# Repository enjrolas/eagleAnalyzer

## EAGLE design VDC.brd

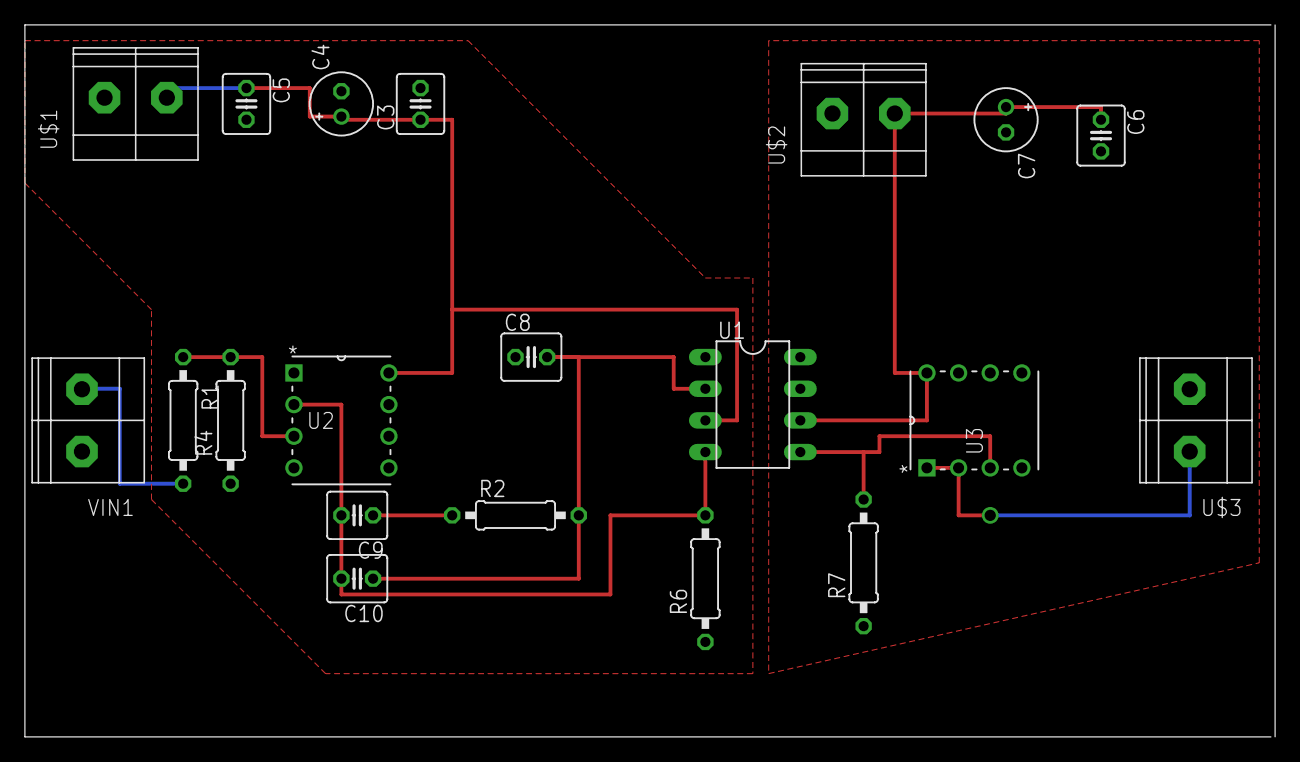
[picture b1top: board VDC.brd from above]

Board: 2 copper layers, 100.3 x 57.1 mm, 20 parts (0 on the bottom side), 11 nets.

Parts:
C3, C5, C6, C8, C9, C10: C025-040X050
C4, C7: E2-5
R1, R2, R4, R6, R7: 0207/10
U1: IL300; DIL08
U2, U3: MCP602-E/P; DIP254P762X508-8P
U$1, U$2, U$3: CTB1500/2; CTB1500-2
VIN1: CTB1500/2; CTB1500-2

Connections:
+5V/1: C3.1, C4.+, C5.1, U1.3, U2.8, U$1.P$2
+5V/2: C6.1, C7.+, U1.6, U3.8, U$2.P$2
DC_OUT: U3.1, U3.2, U$3.P$1
DC_SENSE: R1.2, VIN1.P$2
GND1: C3.2, C4.-, C5.2, C8.1, R4.1, R6.1, U1.1, U2.4, U$1.P$1, VIN1.P$1
GND2: C6.2, C7.-, R7.1, U$2.P$1
unnamed: C9.2, C10.2, R6.2, U1.4, U2.2
unnamed: R7.2, U1.5, U3.3
unnamed: C8.2, C10.1, R2.2, U1.2
unnamed: C9.1, R2.1
unnamed: R1.1, R4.2, U2.3

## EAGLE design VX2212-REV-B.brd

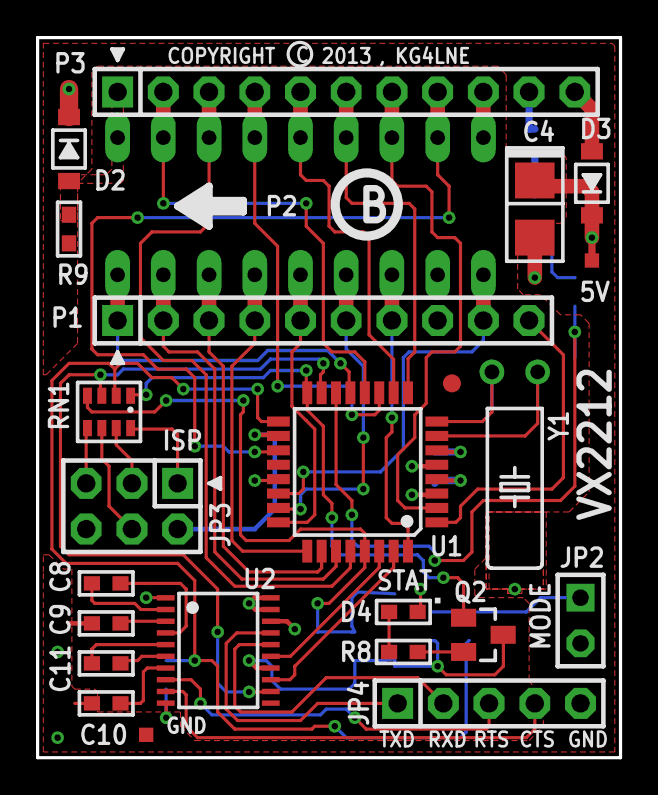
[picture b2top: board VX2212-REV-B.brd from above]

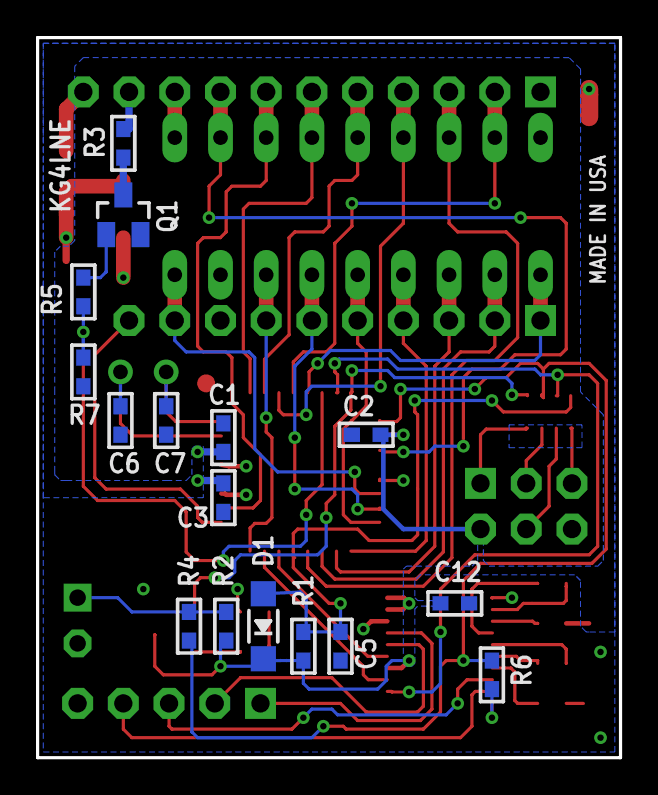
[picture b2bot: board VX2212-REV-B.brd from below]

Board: 2 copper layers, 32.4 x 40.0 mm, 51 parts (16 on the bottom side), 51 nets.

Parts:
5V: TPP-SMD-08SN; SMD-08SN
$$U$1, $$U$2, $$U$3: ICON_PIN1_B
C1, C2, C3, C5, C8, C9, C10, C11, C12: 0.1uF; C0603
C4: 10uF/16V; C3528/T
C6, C7: 22pF; C0603
D1: MMSD4148; SOD123
D2: MBR140SFT1 (DNP); SOD123LF
D3: MBR140SFT1; SOD123LF
D4: LTST-C190GKT; CHIPLED_0603
FIDUCIAL1: G10S
GND: TPP-SMD-08SN; SMD-08SN
ICON2: ICON_ARROW-S
JP2: 961102-6404-AR; JP1
JP3: 961206-6404-AR; AVR-ISP-6
JP4: 1X05
P1: 1X10
P2: DIL18-NS
P3: 1X11
Q1, Q2: MMBT3904LT1; SOT23-BEC
R1, R2, R9: 10k; R0603
R3, R4: 47; R0603
R5: 100; R0603
R6: 47 (DNP); R0603
R7: 100k; R0603
R8: 475; R0603
RN1: 47; 742-8
U1: ATMEGA8-16AU; TQFP32-08
U2: MAX3223PW; TSSOP20
U$1: PCBFEAT-COPYRIGHT-032
U$5: FAB_LETTER_L
U$6: (0, 0); FAB_ARROW_LINE050
U$45: 1.5750; FAB_ARROW_LINE050
U$46: 1.2750; FAB_ARROW_LINE050
U$47: FAB_DOCFIELD_GENERIC
U$52: PCBFEAT-REV-070
Y1: 14.7456 MHZ; TC39H

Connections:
#CS1: P1.7, P2.7, U1.32
#CS2: P1.10, U1.1
#RECALL: P2.10, P3.9
#RESET: C5.2, D1.A, R1.1, RN1.4, U1.29
#STORE: P1.9, P2.9, U1.22
#WE: P2.11, P3.8, U1.19
+5V: 5V.TP, C1.2, C2.2, C3.1, C4.+, C12.2, D1.C, D2.C, D3.C, JP3.2, Q2.C, R1.2, R2.1, U1.4, U1.6, U1.18, U2.14, U2.19, U2.20
A0: P1.6, P2.6, U1.23
A1: P1.5, P2.5, U1.24
A2: P1.4, P2.4, U1.25
A3: P1.3, P2.3, U1.26
A4: P1.2, P2.2, U1.27
A5: P2.16, P3.3, U1.28
A6: P2.17, P3.2, U1.12
A7: P1.1, P2.1, U1.13
CTS: R6.1, U2.10
D1: P2.12, P3.7, U1.2
D2: P2.13, P3.6, U1.9
D3: P2.14, P3.5, U1.10
D4: P2.15, P3.4, U1.11
GND: C1.1, C2.1, C3.2, C4.-, C5.1, C6.1, C7.1, C9.2, C10.2, C12.1, D4.C, GND.TP, JP2.2, JP3.6, JP4.5, P1.8, P2.8, Q1.E, R7.1, R9.1, U1.3, U1.5, U1.21, U2.1, U2.18
LED: Q2.B, RN1.1, U1.16
MODE/CTS: R4.1, R6.2, RN1.2, U1.17
unnamed: JP4.1, U2.17
unnamed: JP3.1, RN1.8
unnamed: C11.2, U2.5
unnamed: D4.A, R8.1
unnamed: JP3.4, RN1.6
unnamed: JP3.3, RN1.7
unnamed: JP4.3, U2.8
unnamed: JP4.2, U2.16
unnamed: C8.2, U2.2
unnamed: C10.1, U2.7
unnamed: C9.1, U2.3
unnamed: C8.1, U2.4
unnamed: C11.1, U2.6
unnamed: P3.10, R3.2
unnamed: D2.A, P2.18, P3.1, R9.2
unnamed: JP4.4, U2.9
unnamed: Q2.E, R8.2
unnamed: Q1.C, R3.1
unnamed: JP2.1, R2.2, R4.2
unnamed: D3.A, P3.11
unnamed: JP3.5, RN1.5
unnamed: Q1.B, R5.1
unnamed: C7.2, U1.8, Y1.2
unnamed: C6.2, U1.7, Y1.1
RRST: R5.2, R7.2, U1.14
RTS: RN1.3, U1.15, U2.12
RXD: U1.30, U2.15
TXD: U1.31, U2.13

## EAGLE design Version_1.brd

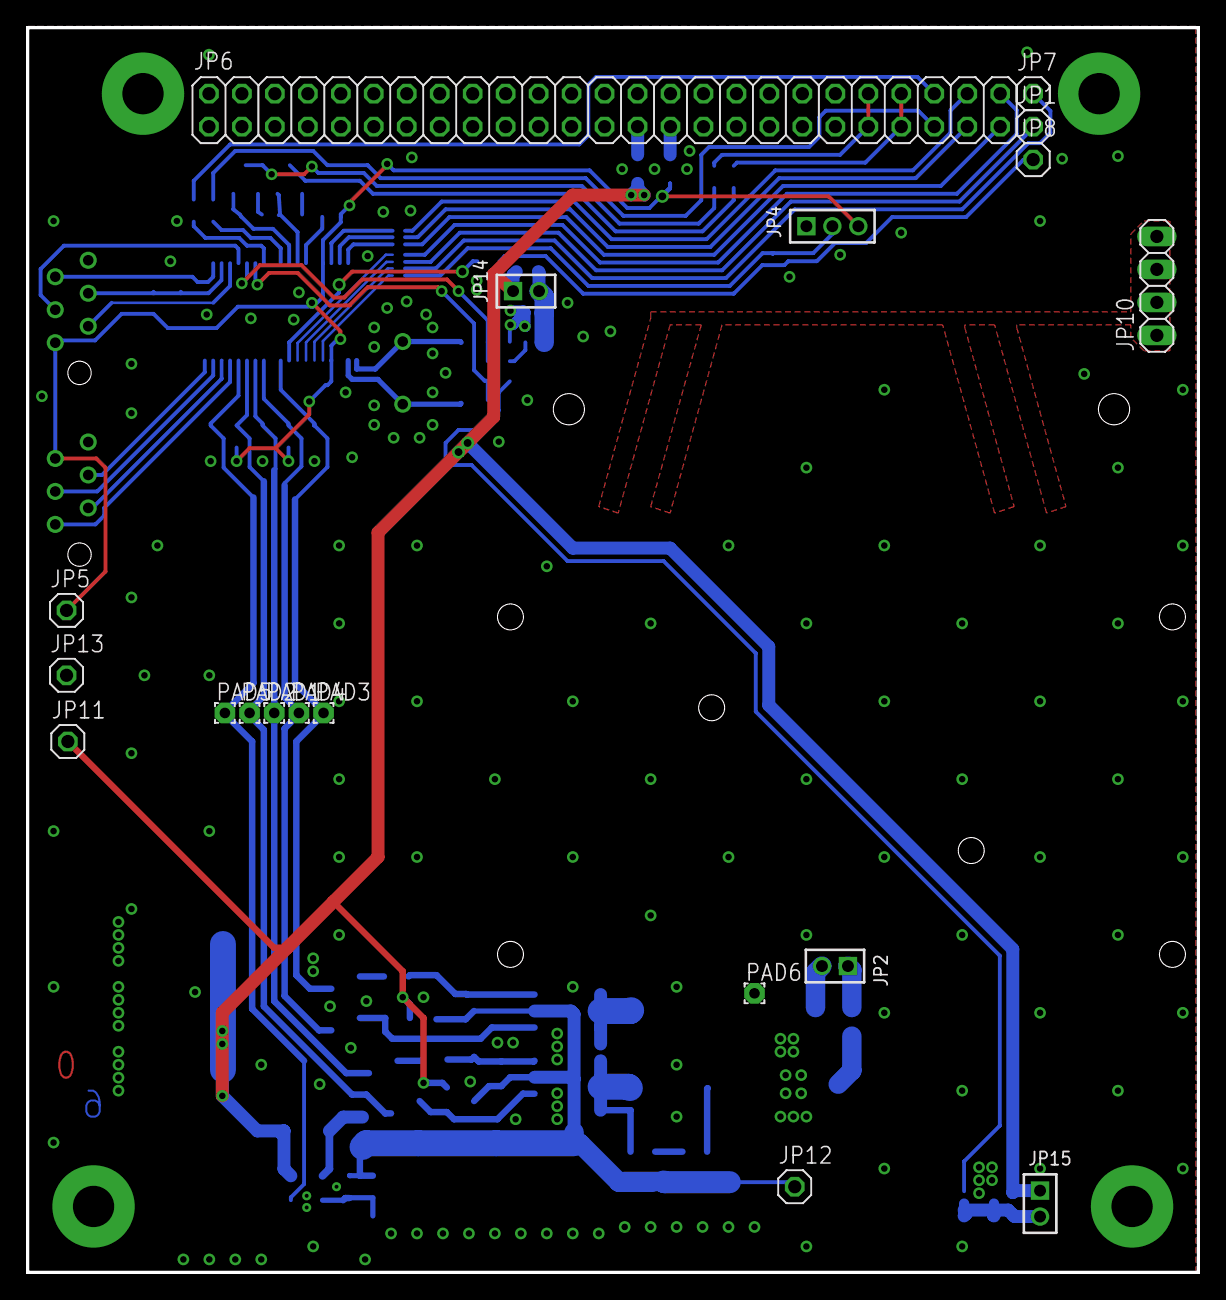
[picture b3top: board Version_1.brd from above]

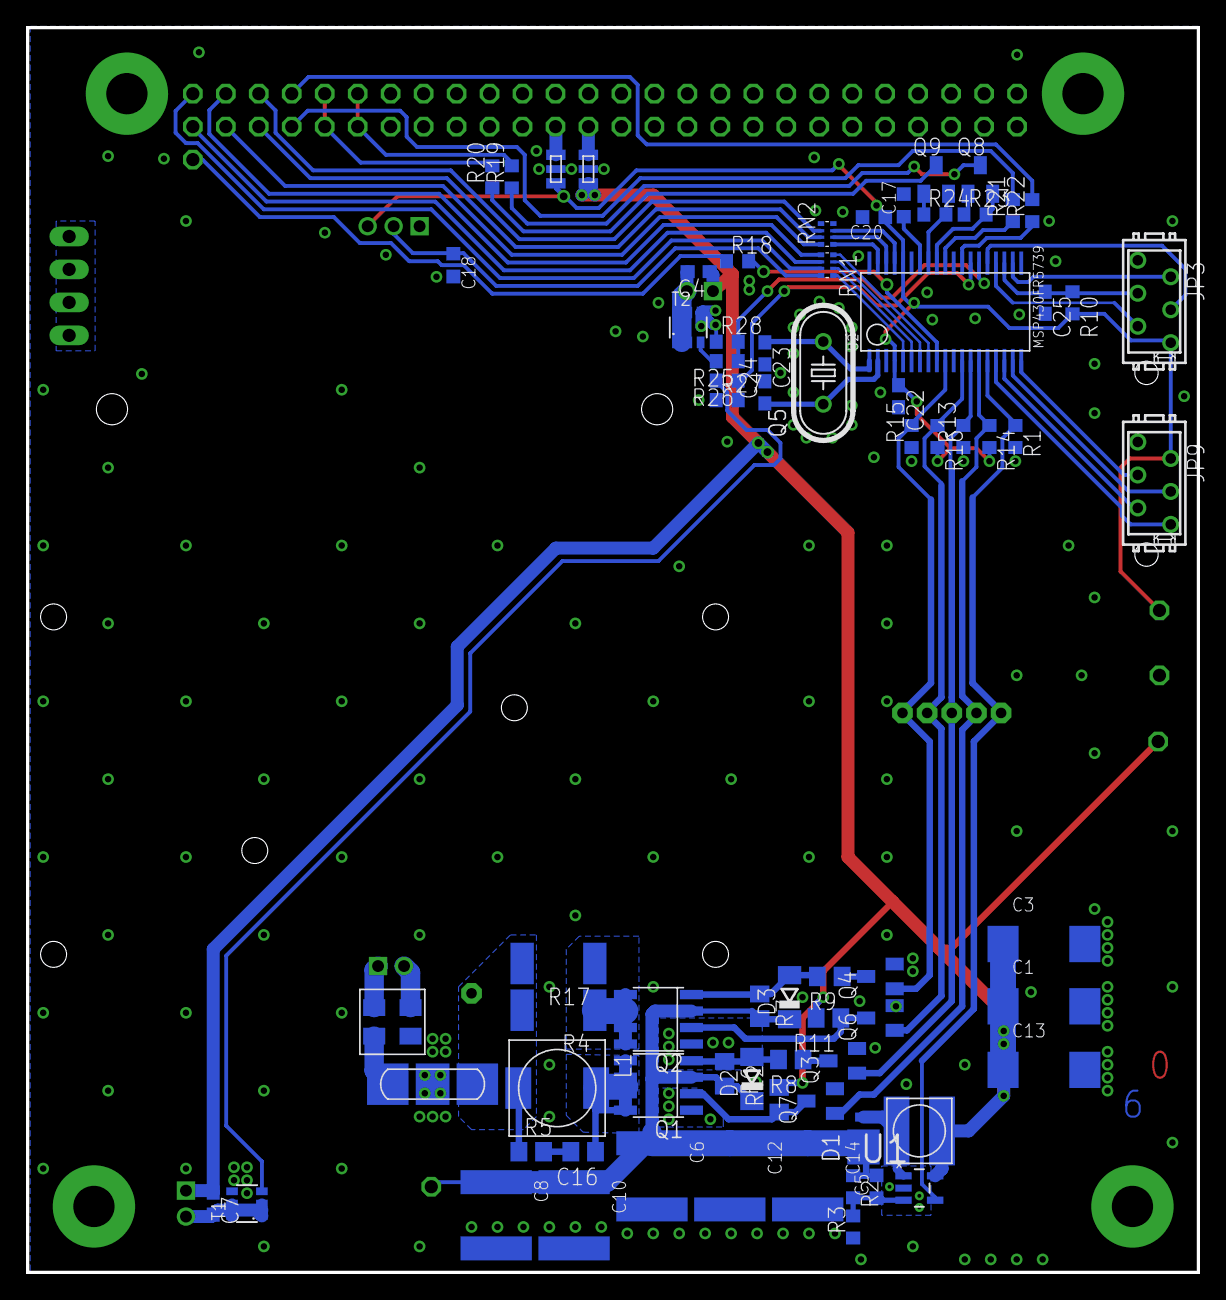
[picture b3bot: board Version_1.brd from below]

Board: 2 copper layers, 90.2 x 95.9 mm, 92 parts (73 on the bottom side), 70 nets.

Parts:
C1, C3, C13: 100u 25V; SMC_E
C4, C7, C22: 100n; C0603
C5: 150p; C0603K
C6, C8, C10, C12, C14: 15u 100V; C2220K
C16: 2n2; C0805
C17: 1u; C0603K
C18, C20: 100n; C0603K
C23, C24: 22p; C0603
C25: 4n7; C0603
C26, C27: 100n 25V; 0805-3TERM
D1: MBRM120LT1G; POWERMITE
D2, D3: 9V1; SOD80C
JP1: 51; 1X01
JP2: Motor; 1X02M
JP3: Programming; MICROMATCH-6
JP4: Resistive feedback sensor; 1X03M
JP5, JP11, JP12, JP13: TP; 1X01
JP6: Short_stack; 2X25
JP7: 52; 1X01
JP8: Jumper wire; 1X01
JP9: Debug; MICROMATCH-6
JP10: 1X04
JP14: Reel lock; 1X02M
JP15: Endmass lock; 1X02M
L1: 100u 0.7A; L-SMD-7.3
L2: 4u7 1A2; SRR4011
PAD1, PAD2, PAD3, PAD4, PAD5, PAD6: 1,6/0,8
Q1, Q2: IRF7350; SO08-IRF
Q3, Q4, Q6, Q7, Q8, Q9: BSS123; SOT23
Q5: 8MHz; HC49U-V
R1, R10, R13, R14, R15, R16, R27, R28: 100k; R0603
R2: 330k; R0603
R3: 11k; R0603
R4, R17: 20R; R2512
R5: 100R; R0805
R6, R7: 1k; R0805
R8, R9, R11, R12: 3k3; R0805
R18, R19, R20, R21, R22: 100R; R0603
R23, R24: 10k; R0603
R25, R26: 100; R0603
RN1, RN2: 100R; EXBN8V
T1, T2: SOT23-6
U1: LM2733YMF; SOT95P284X119-5N
U2: MSP430FR5739; TSSOP38
Z1: DLW5BSN351SQ2; DLW5BS
Z2: 4700-005LF; FILTER-PI

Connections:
+12V: C1.+, C3.+, C4.1, C7.1, C13.+, C26.P$1, JP11.1, JP14.1, JP15.1, L2.P$1, R11.2, R12.2, U1.5
CLK: JP9.3, U2.P$18
FB: C18.1, JP4.2, RN1.4
FBBBBBA: C5.1, R2.2, R3.2, U1.3
GND: C1.-, C3.-, C6.2, C8.2, C10.2, C12.2, C13.-, C14.2, C17.2, C18.2, C20.2, C22.2, C23.2, C24.2, C25.2, C26.P$2, C27.P$2, JP3.6, JP4.1, JP6.5, JP6.6, JP6.25, JP6.33, JP6.34, JP6.39, JP6.40, JP9.6, JP13.1, Q1.1, Q2.1, Q3.2, Q4.2, Q6.2, Q7.2, R1.2, R3.1, R13.1, R15.1, R27.1, R28.1, RN2.4, RN2.5, T1.4, T2.4, U1.2, U2.P$3, U2.P$33, U2.P$38, Z1.P$2, Z2.P$2
GNL: PAD2.1, Q7.1, R14.1, U2.P$14
GNR: PAD4.1, Q6.1, R16.1, U2.P$12
GPL: PAD1.1, Q3.1, R13.2, U2.P$13
GPR: PAD3.1, Q4.1, R15.2, U2.P$10
GUN0: JP6.47, RN2.7
GUN1: JP6.48, RN2.6
GUN2: JP6.49, RN2.8
GUN3: JP8.1, R18.1
HV: JP10.1, JP10.2, JP10.3, JP10.4
I_ANODE: JP6.50, RN1.1
I_NEG_TETHER: JP7.1, RN1.3
I_POS_TETHER: JP1.1, RN1.2
LOCK_ENDMASS: R26.1, R27.2, U2.P$26
LOCK_REEL: R25.1, R28.2, U2.P$25
MISO/RX: JP9.2, U2.P$17
unnamed: Q2.2, Q6.3, R11.1
unnamed: C7.2, JP15.2, T1.1, T1.2, T1.5, T1.6
unnamed: R26.2, T1.3
unnamed: C17.1, U2.P$32
unnamed: RN1.5, U2.P$5
unnamed: Q1.2, Q7.3, R12.1
unnamed: C26.P$3, JP6.27
unnamed: D1.2, L2.P$2, U1.1
unnamed: C4.2, JP14.2, T2.1, T2.2, T2.5, T2.6
unnamed: R25.2, T2.3
unnamed: Q9.3, R20.1
unnamed: Q8.3, R19.1
unnamed: C16.2, R5.2
unnamed: C16.1, L1.P$1, Q1.5, Q1.6, Q1.7, Q1.8
unnamed: L1.P$2, PAD6.1, R4.2, R5.1, R17.2, Z2.P$1
unnamed: Q2.5, Q2.6, Q2.7, Q2.8, R4.1, R17.1
unnamed: C27.P$1, JP6.29
unnamed: Q9.2, R24.2, U2.P$31
unnamed: D2.A, Q1.4, R6.1, R8.2
unnamed: Z1.P$3, Z2.P$3
unnamed: D3.A, Q2.4, R7.1, R9.2
unnamed: JP2.1, Z1.P$4
unnamed: Q3.3, R8.1
unnamed: Q4.3, R9.1
unnamed: R22.1, U2.P$27
unnamed: C23.1, Q5.2, U2.P$1
unnamed: C24.1, Q5.1, U2.P$2
unnamed: RN1.6, U2.P$6
unnamed: RN2.1, U2.P$37
unnamed: R21.1, U2.P$29
unnamed: Q8.2, R23.2, U2.P$30
unnamed: RN1.7, U2.P$7
unnamed: JP2.2, Z1.P$1
unnamed: RN1.8, U2.P$8
unnamed: RN2.2, U2.P$36
unnamed: RN2.3, U2.P$35
unnamed: R18.2, U2.P$9
unnamed: JP9.1, U2.P$16
NEGHV: JP6.45, R21.2
POSHV: JP6.46, R22.2
REG_SHDN: PAD5.1, R1.1, U1.4, U2.P$15
RST: C25.1, JP3.4, R10.1, U2.P$22
RXD: JP3.3, U2.P$24
SCL: JP6.43, JP6.44, R20.2
SDA: JP6.41, JP6.42, R19.2
SLAVE: JP9.4, U2.P$19
TEST: JP3.5, U2.P$21
TXD: JP3.2, U2.P$23
V+: C5.2, C6.1, C8.1, C10.1, C12.1, C14.1, D1.1, D2.C, D3.C, JP12.1, Q1.3, Q2.3, R2.1, R6.2, R7.2
VCC: C20.1, C22.1, C27.P$3, JP3.1, JP4.3, JP5.1, JP9.5, Q8.1, Q9.1, R10.2, R14.2, R16.2, R23.1, R24.1, U2.P$4, U2.P$34

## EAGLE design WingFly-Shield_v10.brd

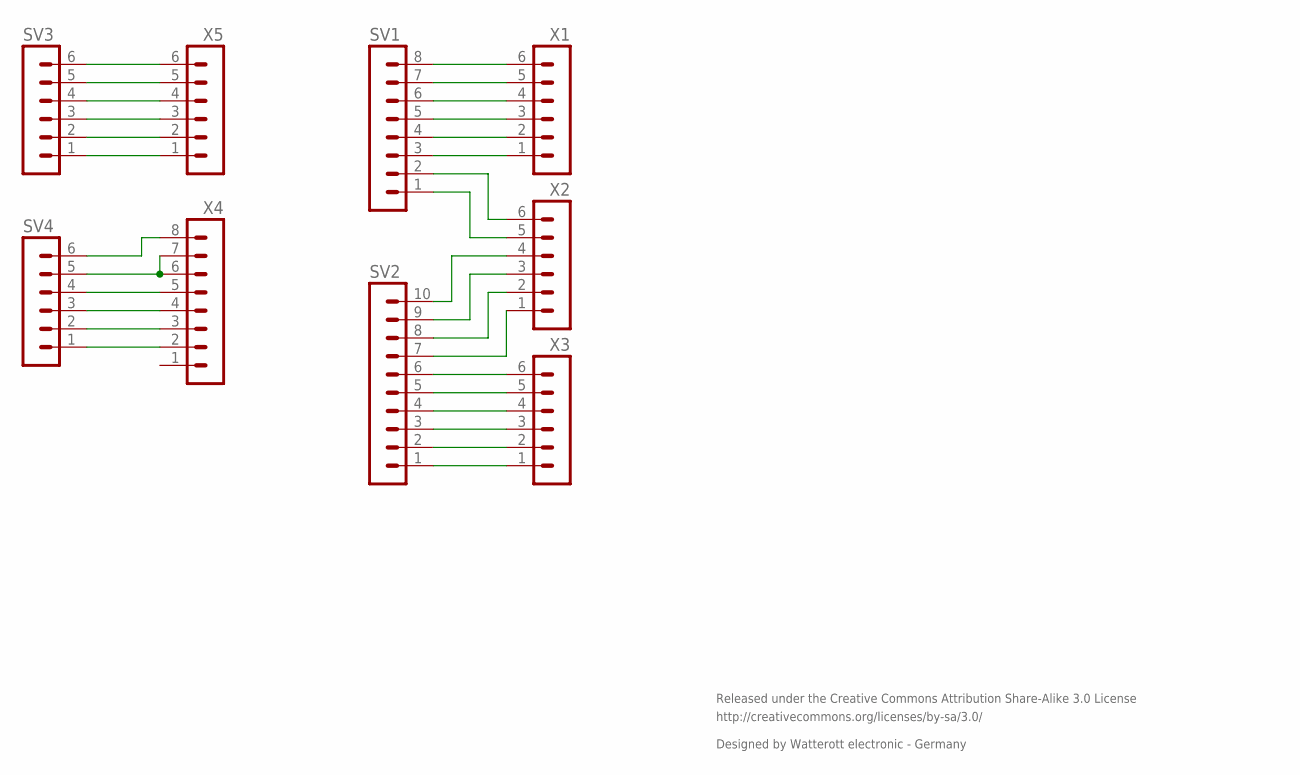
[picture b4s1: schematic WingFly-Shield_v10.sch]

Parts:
SV1: MA08-1
SV2: MA10-1
SV3, SV4: MA06-1
X1, X2, X3, X5: MA06-1
X4: MA08-1

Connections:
3V3: SV4.3, X4.4
5V: SV4.4, X4.5
A0: SV3.1, X5.1
A1: SV3.2, X5.2
A2: SV3.3, X5.3
A3: SV3.4, X5.4
A4: SV3.5, X5.5
A5: SV3.6, X5.6
AREF: SV2.3, X3.3
D0: SV1.8, X1.6
D1: SV1.7, X1.5
D2: SV1.6, X1.4
D3: SV1.5, X1.3
D4: SV1.4, X1.2
D5: SV1.3, X1.1
D6: SV1.2, X2.6
D7: SV1.1, X2.5
D8: SV2.10, X2.4
D9: SV2.9, X2.3
D10: SV2.8, X2.2
D11: SV2.7, X2.1
D12: SV2.6, X3.6
D13: SV2.5, X3.5
GND: SV4.5, X4.6, X4.7
GND2: SV2.4, X3.4
IOREF: SV4.1, X4.2
RST: SV4.2, X4.3
SCL: SV2.1, X3.1
SDA: SV2.2, X3.2
VIN: SV4.6, X4.8

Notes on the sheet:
Released under the Creative Commons Attribution Share-Alike 3.0 License
http://creativecommons.org/licenses/by-sa/3.0/
Designed by Watterott electronic - Germany

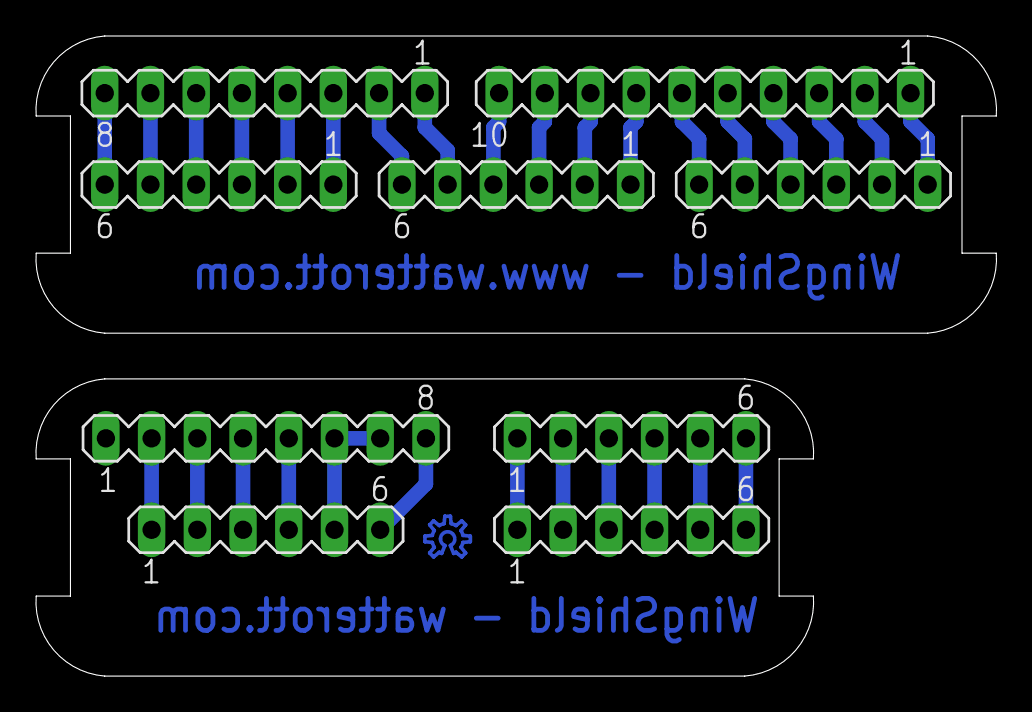
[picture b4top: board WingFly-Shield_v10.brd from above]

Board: 2 copper layers, 53.4 x 35.6 mm, 9 parts (0 on the bottom side), 30 nets.

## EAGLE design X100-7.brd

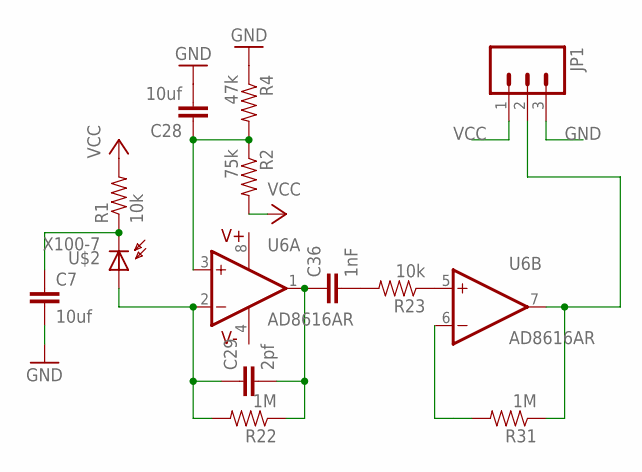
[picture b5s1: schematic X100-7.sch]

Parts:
C7, C28: 10uf; 1206
C29: 2pf; 1206
C36: 1nF; 1206
JP1: M03PTH; 1X03
R1, R23: 10k; 1206
R2: 75k; 1206
R4: 47k; 1206
R22, R31: 1M; 1206
U6: AD8616AR; SOIC8
U$2: X100-7; CERPIN

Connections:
GND: C7.2, C28.2, JP1.3, R4.1
unnamed: C7.1, R1.1, U$2.2
unnamed: C28.1, R2.1, R4.2, U6.3 (+IN)
unnamed: C29.1, R22.2, U6.2 (-IN), U$2.1
unnamed: C36.2, R23.2
unnamed: R31.2, U6.6 (-IN)
unnamed: R23.1, U6.5 (+IN)
unnamed: C29.2, C36.1, R22.1, U6.1 (OUT)
unnamed: JP1.2, R31.1, U6.7 (OUT)
V+: U6.8 (V+)
V-: U6.4 (V-)
VCC: JP1.1, R1.2, R2.2

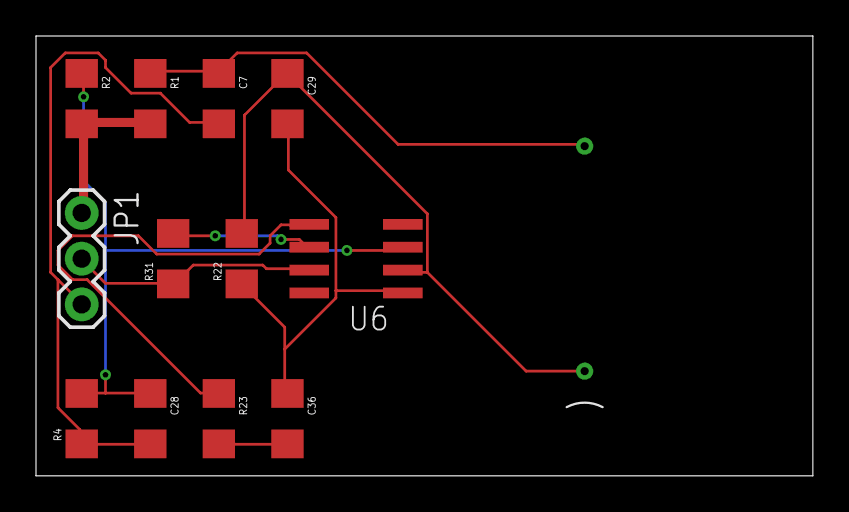
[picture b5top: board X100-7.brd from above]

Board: 2 copper layers, 43.2 x 24.4 mm, 13 parts (0 on the bottom side), 10 nets.

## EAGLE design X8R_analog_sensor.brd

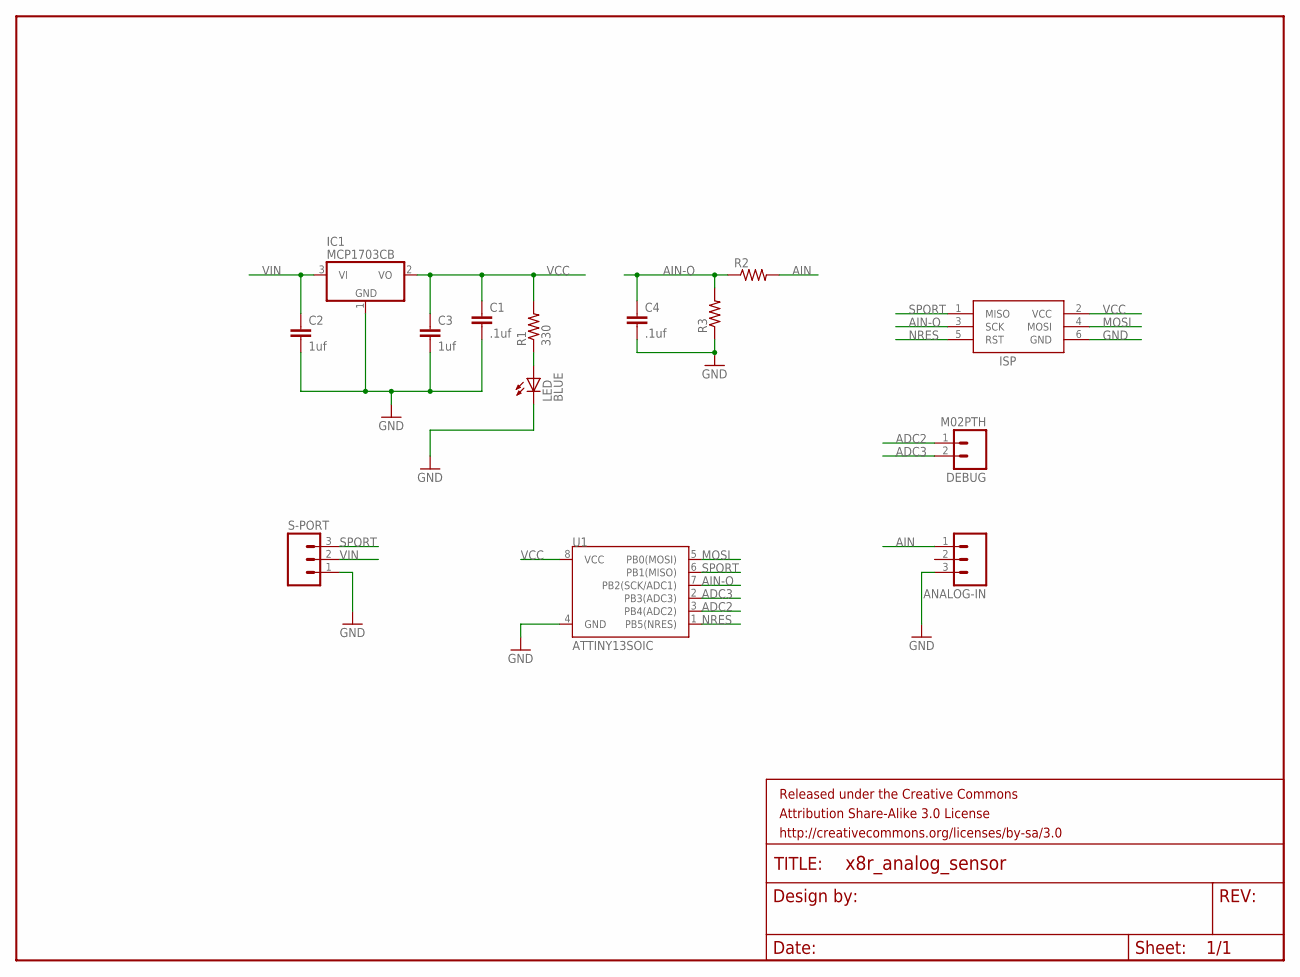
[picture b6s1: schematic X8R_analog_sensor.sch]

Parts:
ANALOG-IN: M03PTH; 1X03
C1, C4: .1uf; 0603-CAP
C2, C3: 1uf; 0603-CAP
DEBUG: M02PTH; 1X02
FRAME1: FRAME-LETTER; CREATIVE_COMMONS
IC1: MCP1703CB; SOT23
ISP: AVRISP-6; AVRISP
LED: BLUE; LED-0603
R1: 330; 0603-RES
R2, R3: RESISTORPTH-1/6W; 1/6W-RES
S-PORT: M03PTH; 1X03
U1: ATTINY13SOIC; SO08

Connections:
ADC2: DEBUG.1, U1.3 (PB4(ADC2))
ADC3: DEBUG.2, U1.2 (PB3(ADC3))
AIN: ANALOG-IN.1, R2.2
AIN-O: C4.1, ISP.3 (SCK), R2.1, R3.2, U1.7 (PB2(SCK/ADC1))
GND: ANALOG-IN.3, C1.2, C2.2, C3.2, C4.2, IC1.1 (GND), ISP.6 (GND), LED.C, R3.1, S-PORT.1, U1.4 (GND)
MOSI: ISP.4 (MOSI), U1.5 (PB0(MOSI))
unnamed: LED.A, R1.1
NRES: ISP.5 (RST), U1.1 (PB5(NRES))
SPORT: ISP.1 (MISO), S-PORT.3, U1.6 (PB1(MISO))
VCC: C1.1, C3.1, IC1.2 (VO), ISP.2 (VCC), R1.2, U1.8 (VCC)
VIN: C2.1, IC1.3 (VI), S-PORT.2

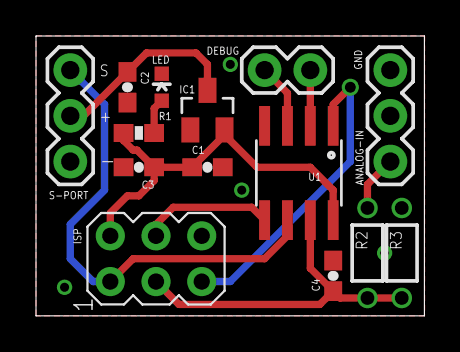
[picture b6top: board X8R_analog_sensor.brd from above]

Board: 2 copper layers, 21.6 x 15.5 mm, 15 parts (0 on the bottom side), 11 nets.

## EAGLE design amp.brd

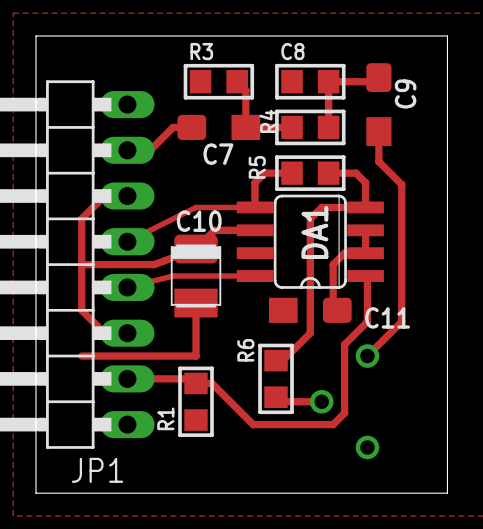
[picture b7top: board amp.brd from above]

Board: 2 copper layers, 22.9 x 25.4 mm, 13 parts (1 on the bottom side), 12 nets.

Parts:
C7, C11: 1uF; SMC_A
C8: 10n; C0805
C9: 10uF; SMC_A
C10: 1uF; SMC_B
DA1: LM4871MX; SO08
JP1: 1X08/90
R1, R3, R4: 22K; R0805
R5, R6: 20K; R0805
R7: 100K; RTRIM-3362P

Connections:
GND: C8.2, C10.-, C11.-, DA1.7, JP1.1, JP1.8, R1.1, R3.1, R7.3
unnamed: DA1.1, JP1.2, R1.2
unnamed: C10.+, DA1.6, JP1.3, JP1.6
unnamed: DA1.8, JP1.4
unnamed: C7.+, JP1.7
unnamed: C7.-, R3.2, R4.1
unnamed: C8.1, C9.+, R4.2
unnamed: DA1.4, R5.1, R6.2
unnamed: C9.-, R7.1
unnamed: R6.1, R7.2
unnamed: C11.+, DA1.2, DA1.3
unnamed: DA1.5, JP1.5, R5.2

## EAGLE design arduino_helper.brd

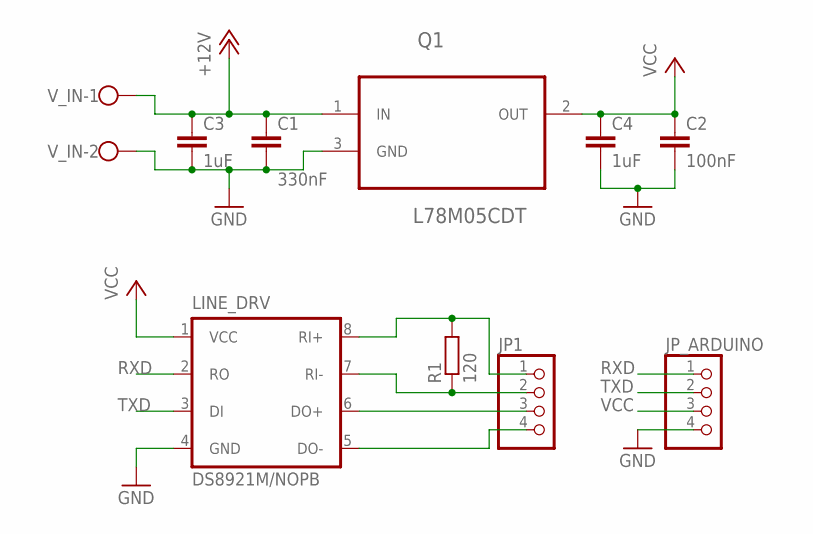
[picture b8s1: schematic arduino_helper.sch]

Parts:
C1: 330nF; C0805
C2: 100nF; C0805
C3, C4: 1uF; C0805
JP1: PINHD-1X4; 1X04
JP_ARDUINO: PINHD-1X4; 1X04
LINE_DRV: DS8921M/NOPB; SOIC8
Q1: L78M05CDT; TO225P972X240-3N
R1: 120; R0805
V_IN: W237-102

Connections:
+12V: C1.1, C3.1, Q1.1 (IN), V_IN.1
GND: C1.2, C2.2, C3.2, C4.2, JP_ARDUINO.4, LINE_DRV.4 (GND), Q1.3 (GND), V_IN.2
unnamed: JP1.2, LINE_DRV.7 (RI-), R1.1
unnamed: JP1.1, LINE_DRV.8 (RI+), R1.2
unnamed: JP1.4, LINE_DRV.5 (DO-)
unnamed: JP1.3, LINE_DRV.6 (DO+)
RXD: JP_ARDUINO.1, LINE_DRV.2 (RO)
TXD: JP_ARDUINO.2, LINE_DRV.3 (DI)
VCC: C2.1, C4.1, JP_ARDUINO.3, LINE_DRV.1 (VCC), Q1.2 (OUT)

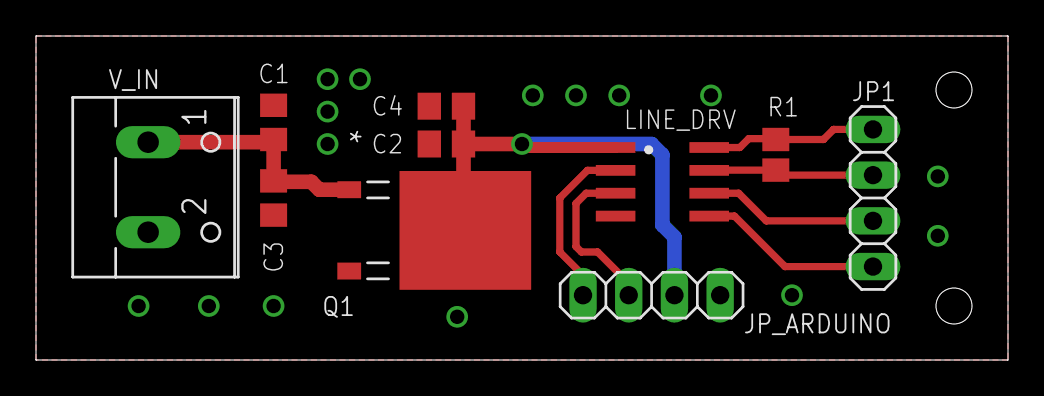
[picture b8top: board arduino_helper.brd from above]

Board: 2 copper layers, 54.0 x 18.0 mm, 10 parts (0 on the bottom side), 9 nets.

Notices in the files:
VX2212-REV-B.brd:
COPYRIGHT: , KG4LNE
parts and their libraries:
dpcb-feature: Copyright Field
Set copyright by text with global attribute >COMPANY
SparkFun-Resistors: Licensing: CC v3.0 Share-Alike You are welcome to use this library for commercial purposes.
rc-master-smd: Copyright (C) 2007, Bob Starr
